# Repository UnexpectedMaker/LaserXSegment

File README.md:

# LaserXSegment Display Library
An API that lets you display numbers and letters on LaserXSegment RGB LED displays that are available from [tindie](https://www.tindie.com/products/seonr/laser-segment-display/)

You can find the Open Source hardware PCB design and Gerber files here too as well as the DXF laser cut design files

## Installing and Use
The downloaded code should be added to your arduino IDE libraries folder, and the library requires the [Adafruit NeoPixel library](https://github.com/adafruit/Adafruit_NeoPixel) for it to function.

To include the LaserXSegment library in your project:

    #include <LaserXSegment.h>

You can then initialise the display with the following line that includes the number of Laser7Segment digits and the GPIO to control them:

    LaserXSegment disp( 5, 4 );

You then start the display with the bebin method, passing the brightness:

    disp.Begin(80);

The you simply pass the display the String you would like displayed and a color:

    disp.DisplayText( "1234", disp.Color( 255,0,0) );

Enjoy!

# Support Unexpected Maker

I love designing, making and releasing our projects as open source. I do it because I believe it’s important to share knowledge and give back to the community, like many have done before me. It helps us all learn and grow.

That said, a lot of time, effort and finances have gone into designing and releasing these files, so please consider supporting me by buy some of my TiinyPICO products:

https://tinypico.com/shop

Or by buying one of our products on tindie:

https://www.tindie.com/stores/seonr/

Or by becoming a Patron:

https://www.patreon.com/unexpectedmaker

# Unexpected Maker
http://youtube.com/c/unexpectedmaker

http://twitter.com/unexpectedmaker

https://www.facebook.com/unexpectedmaker/

https://www.instagram.com/unexpectedmaker/

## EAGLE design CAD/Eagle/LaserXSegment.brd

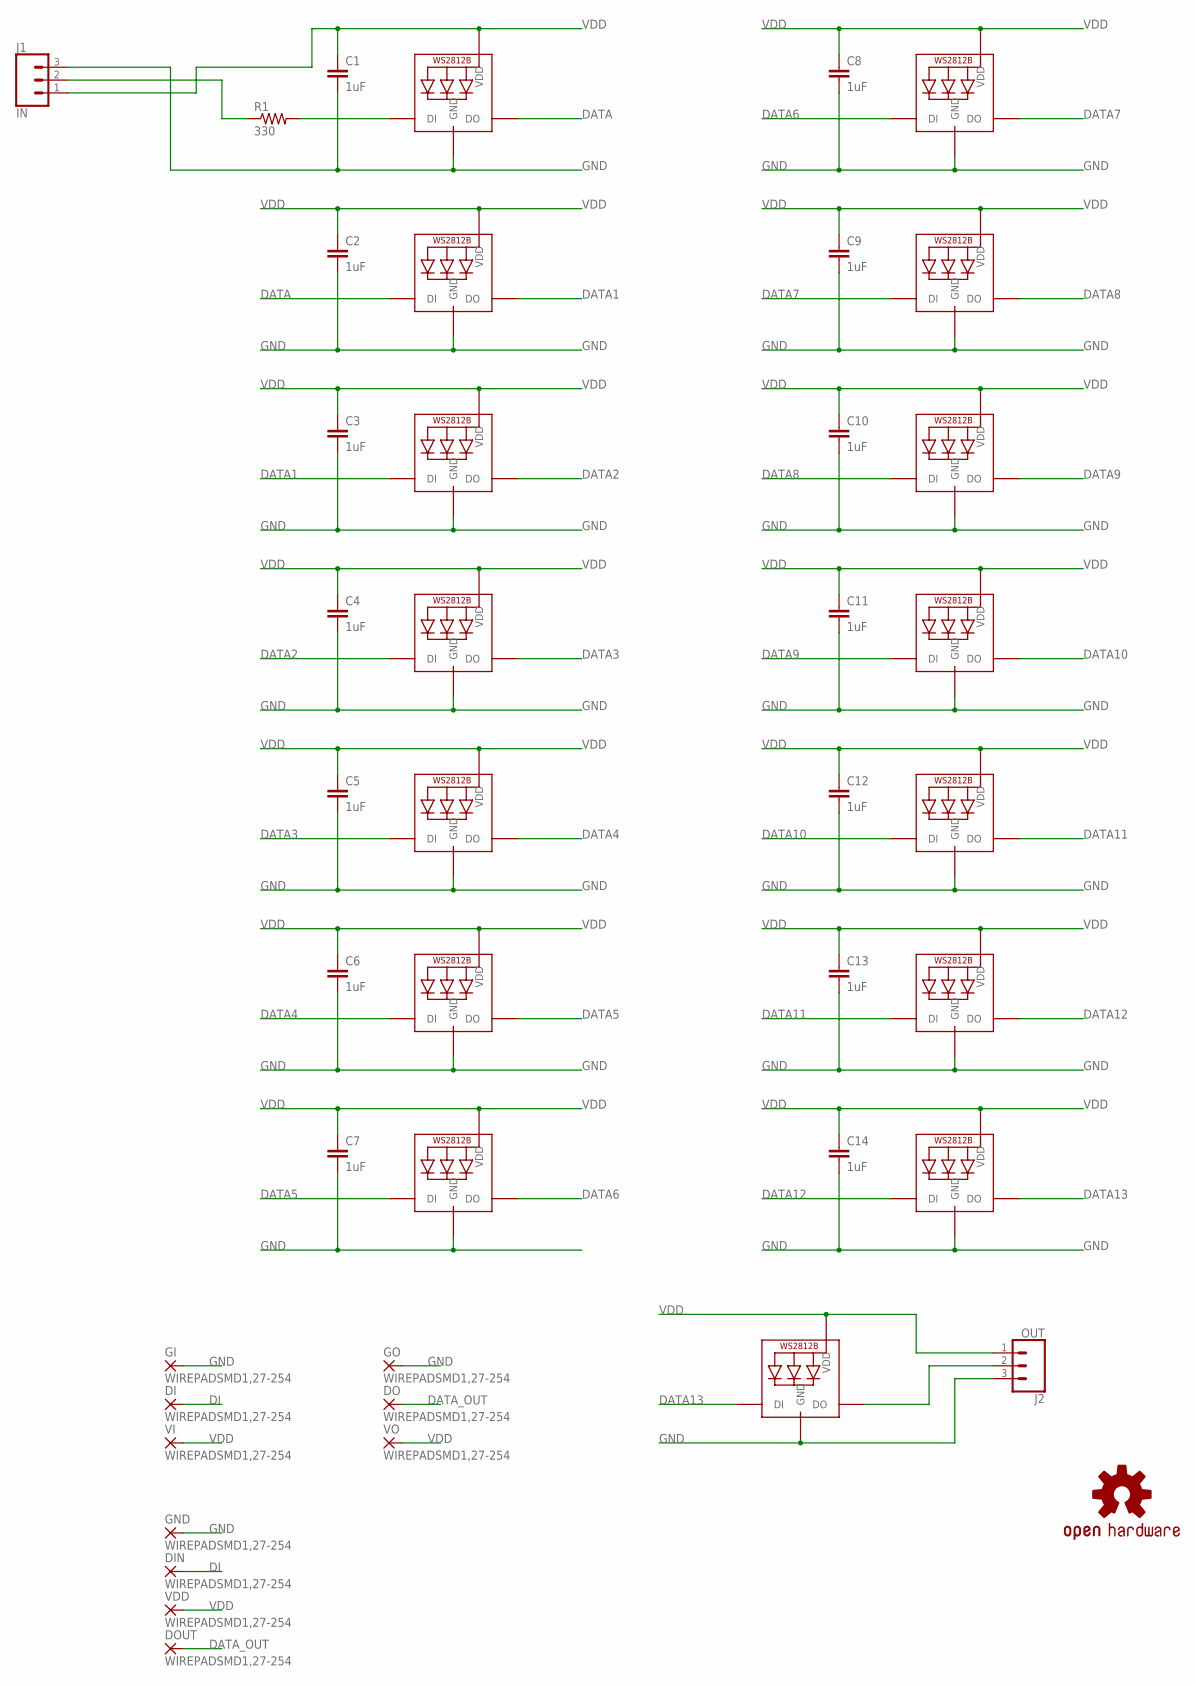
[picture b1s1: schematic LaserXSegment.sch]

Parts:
C1, C2, C3, C4, C5, C6, C7, C8, C9, C10, C11, C12, C13, C14: 1uF; C0805
DI: WIREPADSMD1,27-254; SMD1,27-2,54
DIN: WIREPADSMD1,27-254; SMD1,27-2,54
DO: WIREPADSMD1,27-254; SMD1,27-2,54
DOUT: WIREPADSMD1,27-254; SMD1,27-2,54
GI: WIREPADSMD1,27-254; SMD1,27-2,54
GND: WIREPADSMD1,27-254; SMD1,27-2,54
GO: WIREPADSMD1,27-254; SMD1,27-2,54
J1: IN; 1X03_LONGPADS
J2: OUT; 1X03_LONGPADS
L1, L2, L3, L4, L5, L6, L7, L8, L9, L10, L11, L12, L13, L14: WS2812B5050; WS2812B
L15: RGB 3535; LED3535
LOGO1: OSHW-LOGOM; OSHW-LOGO-M
R1: 330; R0805
VDD: WIREPADSMD1,27-254; SMD1,27-2,54
VI: WIREPADSMD1,27-254; SMD1,27-2,54
VO: WIREPADSMD1,27-254; SMD1,27-2,54

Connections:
DATA: L1.2-DOUT (DO), L2.4-DIN (DI)
DATA1: L2.2-DOUT (DO), L3.4-DIN (DI)
DATA2: L3.2-DOUT (DO), L4.4-DIN (DI)
DATA3: L4.2-DOUT (DO), L5.4-DIN (DI)
DATA4: L5.2-DOUT (DO), L6.4-DIN (DI)
DATA5: L6.2-DOUT (DO), L7.4-DIN (DI)
DATA6: L7.2-DOUT (DO), L8.4-DIN (DI)
DATA7: L8.2-DOUT (DO), L9.4-DIN (DI)
DATA8: L9.2-DOUT (DO), L10.4-DIN (DI)
DATA9: L10.2-DOUT (DO), L11.4-DIN (DI)
DATA10: L11.2-DOUT (DO), L12.4-DIN (DI)
DATA11: L12.2-DOUT (DO), L13.4-DIN (DI)
DATA12: L13.2-DOUT (DO), L14.4-DIN (DI)
DATA13: L14.2-DOUT (DO), L15.1 (DI)
DATA_OUT: DO.1, DOUT.1, J2.2, L15.3 (DO)
DI: DI.1, DIN.1, J1.2, R1.1
DI_R: L1.4-DIN (DI), R1.2
GND: C1.2, C2.2, C3.2, C4.2, C5.2, C6.2, C7.2, C8.2, C9.2, C10.2, C11.2, C12.2, C13.2, C14.2, GI.1, GND.1, GO.1, J1.3, J2.3, L1.3-GND (GND), L2.3-GND (GND), L3.3-GND (GND), L4.3-GND (GND), L5.3-GND (GND), L6.3-GND (GND), L7.3-GND (GND), L8.3-GND (GND), L9.3-GND (GND), L10.3-GND (GND), L11.3-GND (GND), L12.3-GND (GND), L13.3-GND (GND), L14.3-GND (GND), L15.4 (GND)
VDD: C1.1, C2.1, C3.1, C4.1, C5.1, C6.1, C7.1, C8.1, C9.1, C10.1, C11.1, C12.1, C13.1, C14.1, J1.1, J2.1, L1.1-VDD (VDD), L2.1-VDD (VDD), L3.1-VDD (VDD), L4.1-VDD (VDD), L5.1-VDD (VDD), L6.1-VDD (VDD), L7.1-VDD (VDD), L8.1-VDD (VDD), L9.1-VDD (VDD), L10.1-VDD (VDD), L11.1-VDD (VDD), L12.1-VDD (VDD), L13.1-VDD (VDD), L14.1-VDD (VDD), L15.2 (VDD), VDD.1, VI.1, VO.1

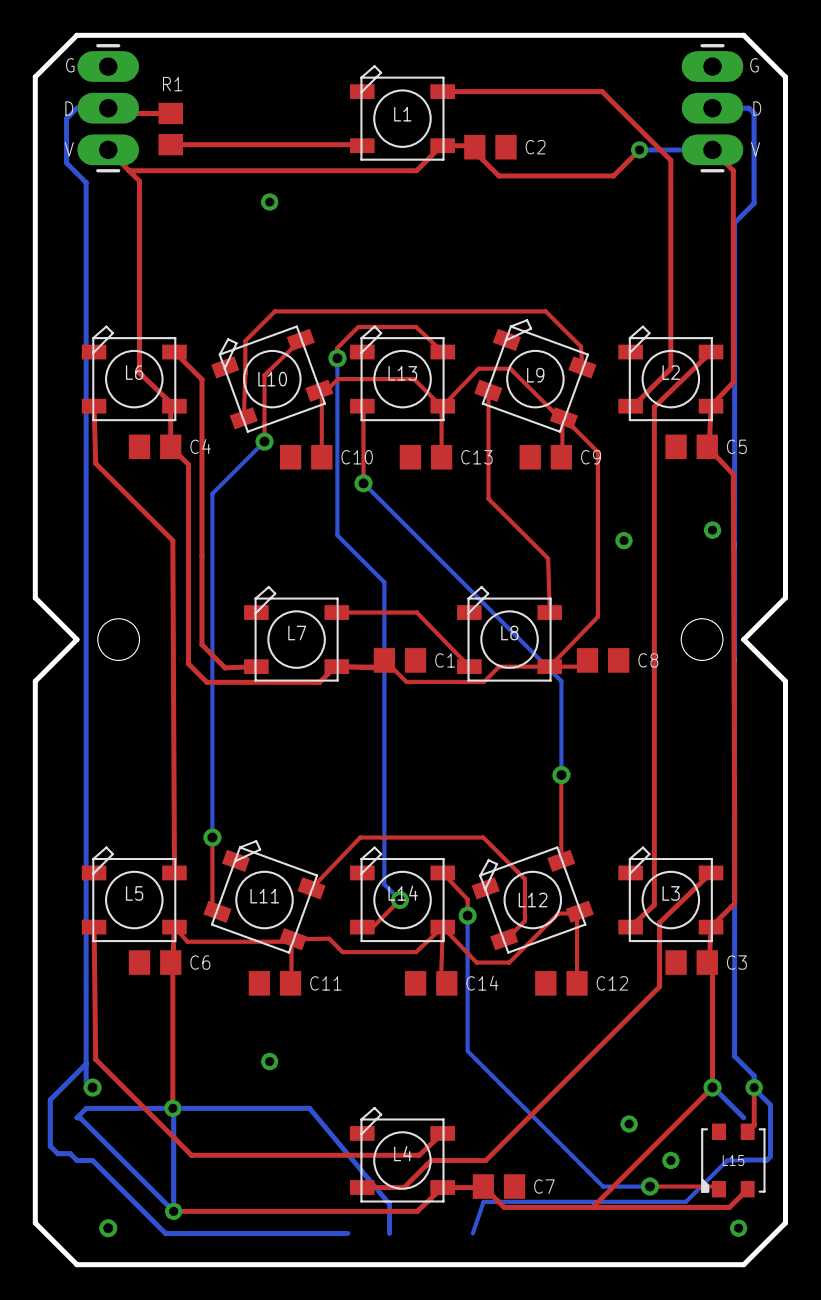
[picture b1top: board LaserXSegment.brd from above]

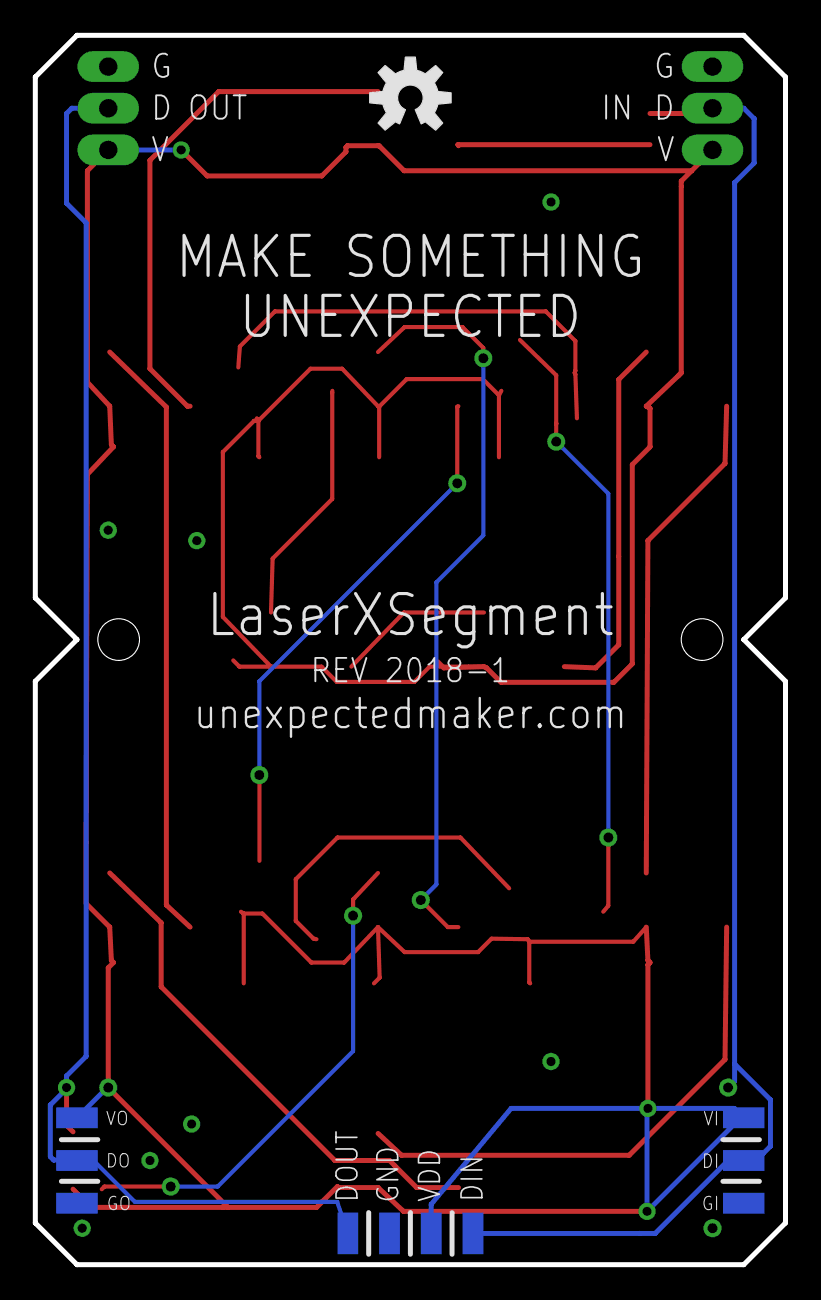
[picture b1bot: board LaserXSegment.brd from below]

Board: 2 copper layers, 45.7 x 74.9 mm, 43 parts (11 on the bottom side), 19 nets.

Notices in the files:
parts and their libraries:
SparkFun-Connectors: Licensing: Creative Commons ShareAlike 4.0 International - https://creativecommons.org/licenses/by-sa/4.0
